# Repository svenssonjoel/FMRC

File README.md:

# FMRC (Work in progress)
Four Motor Robot Controller.

## General videos

[FMRC: UART communication between NRF52 and STM32!](https://youtu.be/KaF7SMBezBs)

## Firmware

### STM32F4 
* Work in progress

### NRF52
* TODO Start

* PROGRAMMING NRF52 stlink:  openocd -f interface/stlink.cfg -f target/nrf52.cfg

telnet localhost 4444
 > reset 
 > program zephyr.hex verify 

# V1_0

## Hardware

## PCBs arrived

## Ready to start testing

# V2_0

Work on version 2.0 is in progress. 

[FMRC V2 PART 14: First draft of completely routed PCB](https://youtu.be/DmLaImre3FM)

[FMRC V2 PART 13: More routing -- finishing off at the DRV8848 area](https://youtu.be/Vftj-5NWg6g )

[FMRC V2 PART 12: Starting to route in the DRV8848 area](https://youtu.be/RzzjTzkN7RY)

[FMRC V2 PART 11: More PCB routing](https://youtu.be/tmIGIp5ANTw)

[FMRC V2 PART 10: Started routing](https://youtu.be/_2mg14zOH1I)

[FMRC V2 PART 9: Tightening up the placement of components](https://youtu.be/uJEVWuKENiA)

[FMRC V2 PART 8: Roughly sorting components](https://youtu.be/DiCStZvnE-I)

[FMRC V2 PART 7: placing components focusing on the DC-DC area](https://youtu.be/_qIdTwvhaeo)

[FMRC V2 PART 6: Boot modes and Boot-loader that allows USB flashing](https://youtu.be/w9wKbaCBO-c)

[FMRC V2 PART 5: Adding an audio jack and doing some spice simulation in KiCAD](https://youtu.be/Df5hQqESk7Q)

[FMRC V2 PART 4: Servo outputs may be nice to have and finishing off in preparation for routing](https://youtu.be/peYSSjiu5AY)

[FMRC V2 PART 3: Out with the old, in with the new (and some confusion about pins with no net!)](https://youtu.be/iIYXo59sdyU)

[FMRC V2 PART 2B: Adding some caps and experimenting some more with kicad hierarchical labels](https://youtu.be/d1Me0BP48rM)

[FMRC V2 PART 2: Adding DRV8847 chips and trying out KICADs hiearchical labels](https://youtu.be/gP7LMV8jKK8)

[FMRC V2 PART 1: new 5V regulator that can do 3A](https://youtu.be/TqqdmnVX5Wo)

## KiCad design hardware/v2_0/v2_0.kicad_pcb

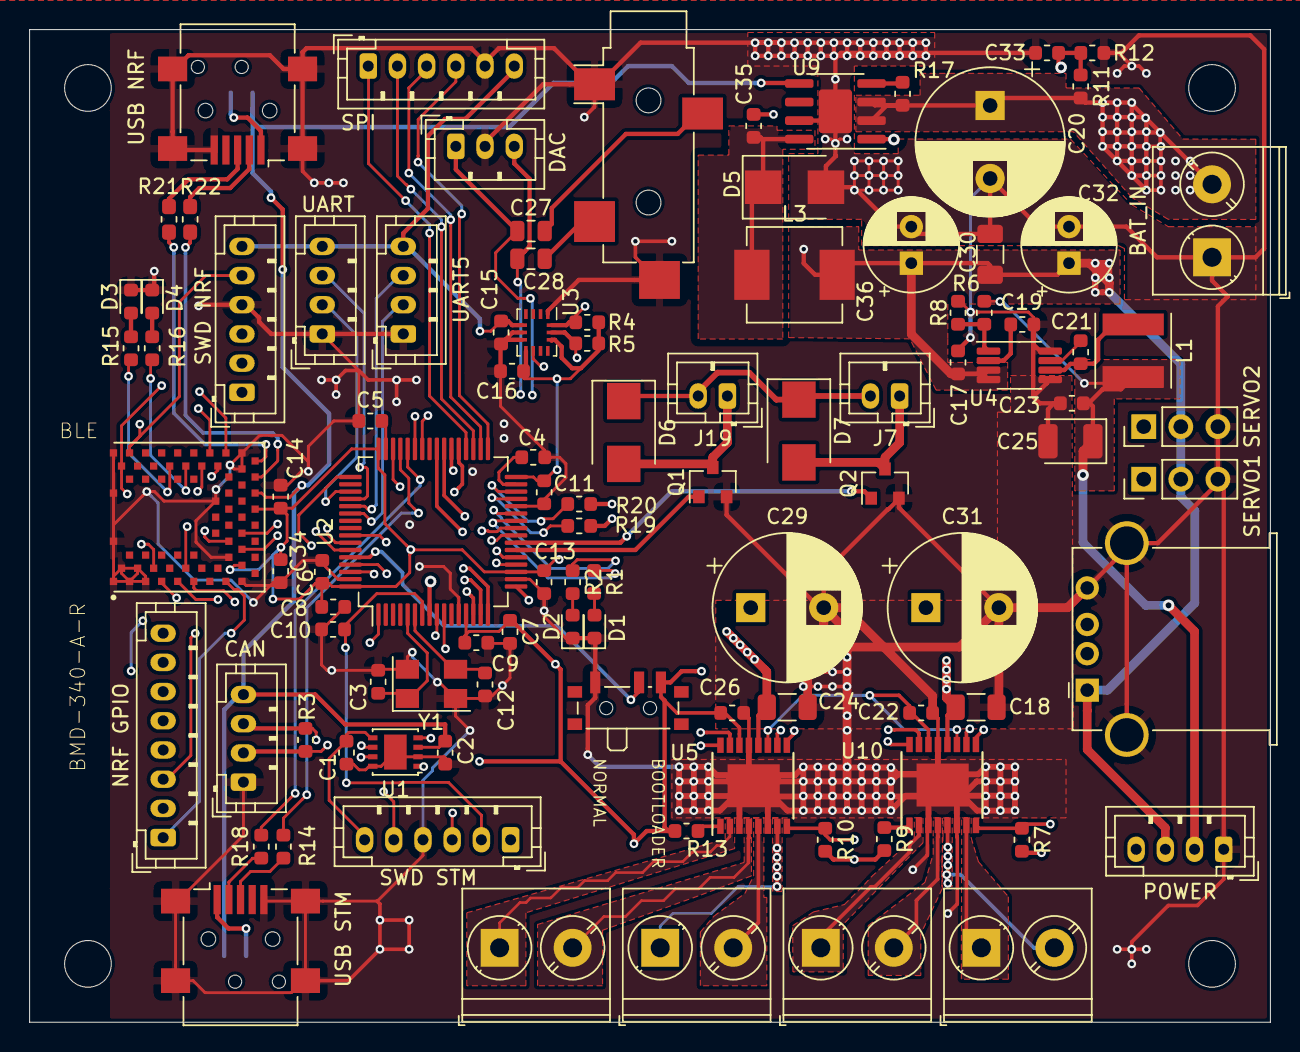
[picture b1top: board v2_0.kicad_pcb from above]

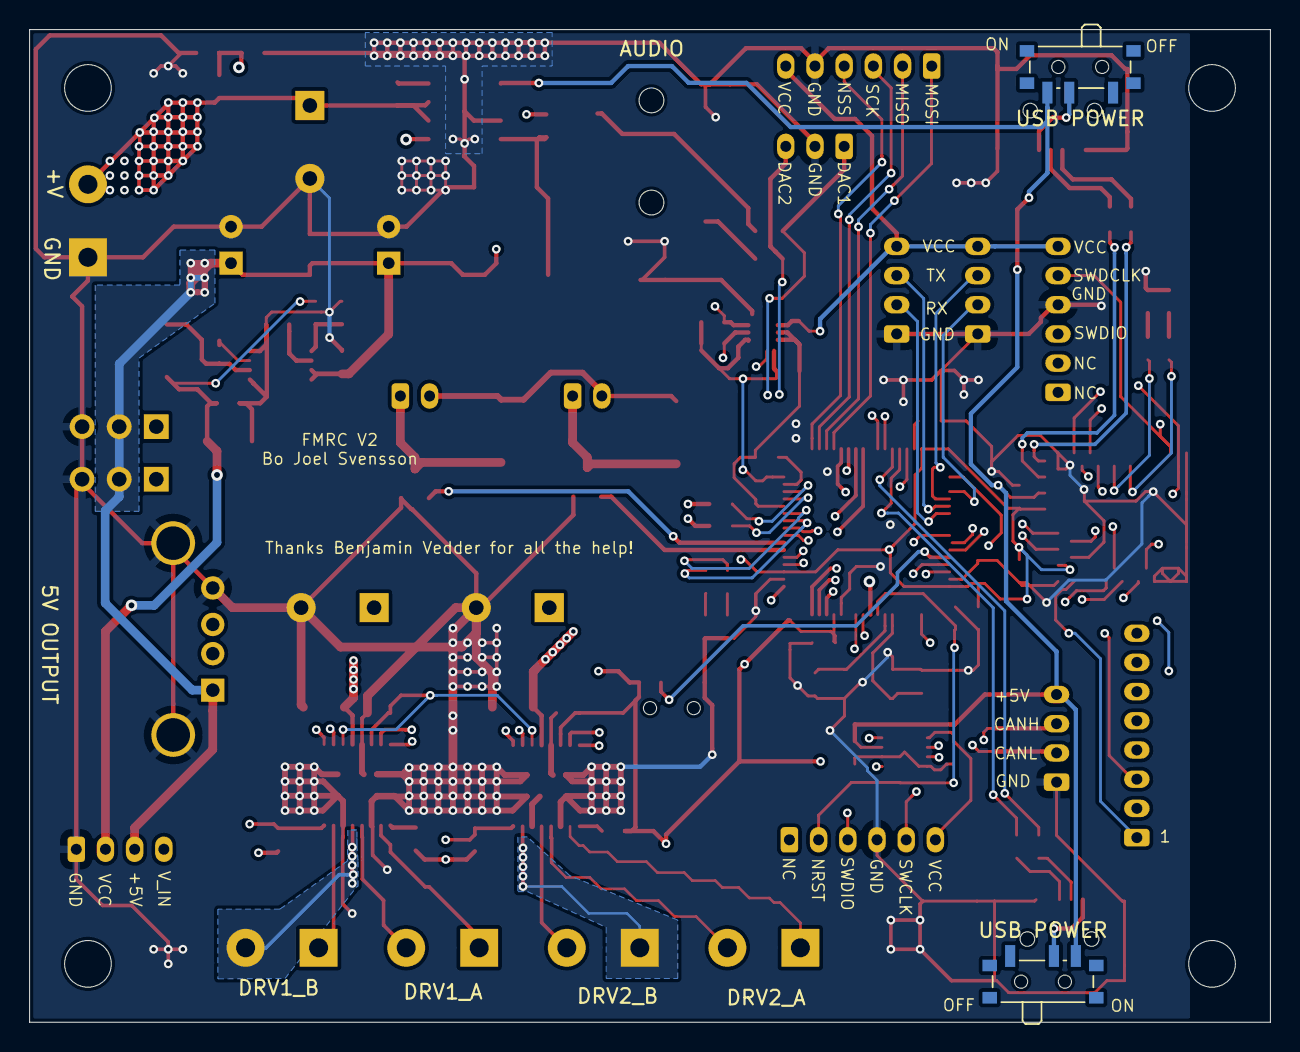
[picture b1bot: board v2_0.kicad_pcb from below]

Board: 4 copper layers, 85.0 x 68.0 mm, 107 parts (2 on the bottom side), 97 nets.

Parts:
5V OUTPUT: USB_A; USB_A_Stewart_SS-52100-001_Horizontal
AUDIO: AudioJack3_Ground; Jack_3.5mm_CUI_SJ-3524-SMT_Horizontal
BAT_IN: Power_terminal; TerminalBlock_Phoenix_PT-1,5-2-5.0-H_1x02_P5.00mm_Horizontal
BLE: BMD-340-A-R; RIGADO_BMD-340-A-R
C1, C2, C4, C5, C6, C7, C8, C9, C11, C13, C14, C15, C16, C17, C19, C22, C23, C26, C33, C34: 2.2u; C_0603_1608Metric
C3, C12: 15p; C_0603_1608Metric
C10, C21: 100n; C_0603_1608Metric
C18, C24, C30: 10uF; C_1206_3216Metric
C20, C29, C31: 100uF; CP_Radial_D10.0mm_P5.00mm
C25: 100u; CP_EIA-3528-12_Kemet-T
C27, C28: 10uF; C_0805_2012Metric
C32, C36: 47uF; CP_Radial_D6.3mm_P2.50mm
C35: 0.1uF; C_0603_1608Metric
CAN: CAN; JST_PH_B4B-PH-K_1x04_P2.00mm_Vertical
D1, D3: RED; LED_0603_1608Metric
D2, D4: GREEN; LED_0603_1608Metric
D5: SSB43L; D_SMB
D6, D7: D_Schottky; D_SMB
DAC: DAC; JST_PH_B3B-PH-K_1x03_P2.00mm_Vertical
DRV1_A, DRV2_A: DRV1_MTR1; TerminalBlock_Phoenix_PT-1,5-2-5.0-H_1x02_P5.00mm_Horizontal
DRV1_B, DRV2_B: DRV1_MTR2; TerminalBlock_Phoenix_PT-1,5-2-5.0-H_1x02_P5.00mm_Horizontal
J7: MTR2_CON; JST_PH_B2B-PH-K_1x02_P2.00mm_Vertical
J19: MTR1_CON; JST_PH_B2B-PH-K_1x02_P2.00mm_Vertical
L1: 22U; L_Taiyo-Yuden_MD-5050
L3: 4,7uH; L_Vishay_IHLP-2525
MK1, MK2, MK3, MK4: Mounting_Hole; MountingHole_3.2mm_M3
NRF GPIO: NRFGPIO; JST_PH_B8B-PH-K_1x08_P2.00mm_Vertical
POWER: PWR; JST_PH_B4B-PH-K_1x04_P2.00mm_Vertical
Q1, Q2: Q_NMOS_GSD; SOT-23
R1, R2, R4, R5, R15, R16: 1k; R_0603_1608Metric
R3, R19, R20: 220R; R_0603_1608Metric
R6: 33k; R_0603_1608Metric
R7, R8, R9, R10, R13: 10k; R_0603_1608Metric
R11: 56k; R_0603_1608Metric
R12: 12k; R_0603_1608Metric
R14, R18: 22R; R_0603_1608Metric
R17: 100k; R_0603_1608Metric
R21, R22: 22R; R_0603_1608Metric_Pad1.05x0.95mm_HandSolder
SERVO1: SERV1; PinHeader_1x03_P2.54mm_Vertical
SERVO2: SERV2; PinHeader_1x03_P2.54mm_Vertical
SPI: SPI; JST_PH_B6B-PH-K_1x06_P2.00mm_Vertical
SW3: BOOT0; SW_SPDT_PCM12
SWD NRF: NRFSWD; JST_PH_B6B-PH-K_1x06_P2.00mm_Vertical
SWD STM: SWD; JST_PH_B6B-PH-K_1x06_P2.00mm_Vertical
U1: TJA1051TK-3; DFN-8-1EP_3x3mm_P0.65mm_EP1.55x2.4mm
U2: STM32F40X_LQFP64; LQFP-64_10x10mm_P0.5mm
U3: BMI160; Bosch_LGA-14_3x2.5mm_P0.5mm
U4: MCP16311/2; MSOP-8_3x3mm_P0.65mm
U5, U10: DRV8848; TSSOP-16-1EP_4.4x5mm_P0.65mm
U9: ADP2303ARDZ-5.0; SOIC-8-1EP_3.9x4.9mm_P1.27mm_EP2.29x3mm
UART: USART3_UART4; JST_PH_B4B-PH-K_1x04_P2.00mm_Vertical
UART5: UART5; JST_PH_B4B-PH-K_1x04_P2.00mm_Vertical
USB NRF: USB_B_Mini; USB_Mini-B_Lumberg_2486_01_Horizontal
USB POWER: NRF_USB_POWER; SW_SPDT_PCM12
USB POWER#2: MCU_USB_POWER; SW_SPDT_PCM12
USB STM: USB_B_Mini; USB_Mini-B_Lumberg_2486_01_Horizontal
Y1: 8M; Crystal_SMD_5032-4Pin_5.0x3.2mm

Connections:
+5V: 5V OUTPUT.1, BLE.66, C2.1, C17.1, C30.1, C32.1, C36.1, CAN.4, L3.2, POWER.3, SERVO1.2, SERVO2.2, U1.3, U4.3, U4.4, U9.5, USB POWER.3, USB POWER#2.3
/DRV1_A1: U2.14, U10.16
/DRV1_A2: U2.15, U10.15
/DRV1_B1: U2.16, U10.9
/DRV1_B2: U2.17, U10.10
/DRV1_NFAULT: R7.1, U2.24, U10.8
/DRV2_A1: U2.37, U5.16
/DRV2_A2: U2.38, U5.15
/DRV2_B1: U2.39, U5.9
/DRV2_B2: U2.40, U5.10
/MTR1_PWM: Q1.1, U2.22
/MTR2_PWM: Q2.1, U2.23
/NFAULT_DRV2: R10.1, U2.25, U5.8
/base_sheet/BOOT0: SW3.2, U2.60
/base_sheet/SERV1: R19.1, U2.29
/base_sheet/SERV2: R20.1, U2.30
/base_sheet/SPI2_MISO: SPI.2, U2.35
/base_sheet/SPI2_MOSI: SPI.1, U2.36
/base_sheet/SPI2_NSS: SPI.4, U2.33
/base_sheet/SPI2_SCK: SPI.3, U2.34
/base_sheet/UART5_RX: U2.54, UART5.2
/base_sheet/UART5_TX: U2.53, UART5.3
CANH: CAN.3, R3.2, U1.7
CANL: CAN.2, R3.1, U1.6
CAN_RX: U1.4, U2.61
CAN_TX: U1.1, U2.62
GND: 5V OUTPUT.4, 5V OUTPUT.5, AUDIO.G, AUDIO.S, BAT_IN.1, BLE.1, BLE.2, BLE.3, BLE.4, BLE.5, BLE.16, BLE.18, BLE.29, BLE.30, BLE.45, BLE.46, BLE.47, BLE.55, C1.2, C2.2, C3.1, C4.1, C5.1, C6.2, C7.2, C8.2, C9.2, C10.2, C11.2, C12.1, C13.2, C14.2, C15.2, C16.2, C17.2, C18.1, C19.2, C20.2, C22.2, C23.2, C24.1, C25.2, C26.2, C29.2, C30.2, C31.2, C32.2, C33.1, C34.2, C36.2, CAN.1, D1.1, D2.1, D3.1, D4.1, D5.2, DAC.2, POWER.1, Q1.2, Q2.2, R8.1, R12.2, SERVO1.3, SERVO2.3, SPI.5, SW3.1, SWD NRF.4, SWD STM.4, U1.2, U1.8, U1.9, U2.12, U2.18, U2.28, U2.63, U3.1, U3.6, U3.7, U4.5, U4.8, U5.3, U5.6, U5.13, U5.17, U9.7, U9.9, U10.3, U10.6, U10.13, U10.17, UART.1, UART5.1, USB NRF.5, USB NRF.6, USB STM.5, USB STM.6, Y1.2, Y1.4
IMU_INT2: BLE.11, U2.57, U3.9
NRFGPIO1: BLE.15, NRF GPIO.1
NRFGPIO2: BLE.19, NRF GPIO.2
NRFGPIO3: BLE.20, NRF GPIO.3
NRFGPIO4: BLE.21, NRF GPIO.4
NRFGPIO5: BLE.31, NRF GPIO.5
NRFGPIO6: BLE.32, NRF GPIO.6
NRFGPIO7: BLE.33, NRF GPIO.7
NRFGPIO8: BLE.34, NRF GPIO.8
NRFRX: BLE.7, U2.42
NRFSWDCLK: BLE.43, SWD NRF.5, U2.10
NRFSWDIO: BLE.44, SWD NRF.3, U2.9
NRFTX: BLE.6, U2.43
NRFUSBD+: BLE.68, R21.2
NRFUSBD-: BLE.67, R22.2
NRST: C10.1, SWD STM.2, U2.7
unnamed: C3.2, U2.5, Y1.1
unnamed: C4.2, U2.31
unnamed: C5.2, U2.47
unnamed: C12.2, U2.6, Y1.3
unnamed: C19.1, U4.2
unnamed: C21.1, U4.7
unnamed: C21.2, L1.1, U4.6
unnamed: C27.1, DAC.1, U2.20
unnamed: AUDIO.R, C27.2
unnamed: C28.1, DAC.3, U2.21
unnamed: AUDIO.T, C28.2
unnamed: C35.1, U9.1
unnamed: C35.2, D5.1, L3.1, U9.8
unnamed: D1.2, R1.2
unnamed: D2.2, R2.2
unnamed: D3.2, R15.2
unnamed: D4.2, R16.2
unnamed: D6.2, J19.1, Q1.3
unnamed: D7.2, J7.1, Q2.3
unnamed: USB POWER#2.2, USB STM.1
unnamed: R18.1, USB STM.2
unnamed: R14.1, USB STM.3
unnamed: DRV1_A.1, U10.2
unnamed: DRV1_A.2, U10.4
unnamed: DRV1_B.1, U10.7
unnamed: DRV1_B.2, U10.5
unnamed: DRV2_A.1, U5.2
unnamed: DRV2_A.2, U5.4
unnamed: R19.2, SERVO1.1
unnamed: R20.2, SERVO2.1
unnamed: USB NRF.1, USB POWER.2
unnamed: R22.1, USB NRF.2
unnamed: R21.1, USB NRF.3
unnamed: DRV2_B.1, U5.7
unnamed: DRV2_B.2, U5.5
unnamed: R1.1, U2.26
unnamed: R2.1, U2.27
unnamed: R6.1, R8.2, U4.1
unnamed: R9.1, U10.1
unnamed: R13.1, U5.1
unnamed: BLE.38, R15.1
unnamed: BLE.36, R16.1
unnamed: R17.2, U9.4
SCL: BLE.10, R5.1, U2.58, U3.13
SDA: BLE.9, R4.1, U2.59, U3.14
SWCLK: SWD STM.5, U2.49
SWDIO: SWD STM.3, U2.46
UART_RXD: U2.51, UART.2
UART_TXD: U2.52, UART.3
USB_DM: R18.2, U2.44
USB_DP: R14.2, U2.45
VCC: BLE.17, BLE.65, C1.1, C6.1, C7.1, C8.1, C9.1, C11.1, C13.1, C14.1, C15.1, C16.1, C22.1, C23.1, C25.1, C26.1, C34.1, L1.2, POWER.2, R4.2, R5.2, R6.2, R7.2, R9.2, R10.2, R13.2, SPI.6, SW3.3, SWD NRF.6, SWD STM.6, U1.5, U2.1, U2.13, U2.19, U2.32, U2.48, U2.64, U3.5, U3.8, U3.12, U5.11, U5.14, U10.11, U10.14, UART.4, UART5.4
V_IN: BAT_IN.2, C18.2, C20.1, C24.2, C29.1, C31.1, D6.1, D7.1, J7.2, J19.2, POWER.4, R11.2, R17.1, U5.12, U9.2, U9.3, U10.12
V_METER: C33.2, R11.1, R12.1, U2.8

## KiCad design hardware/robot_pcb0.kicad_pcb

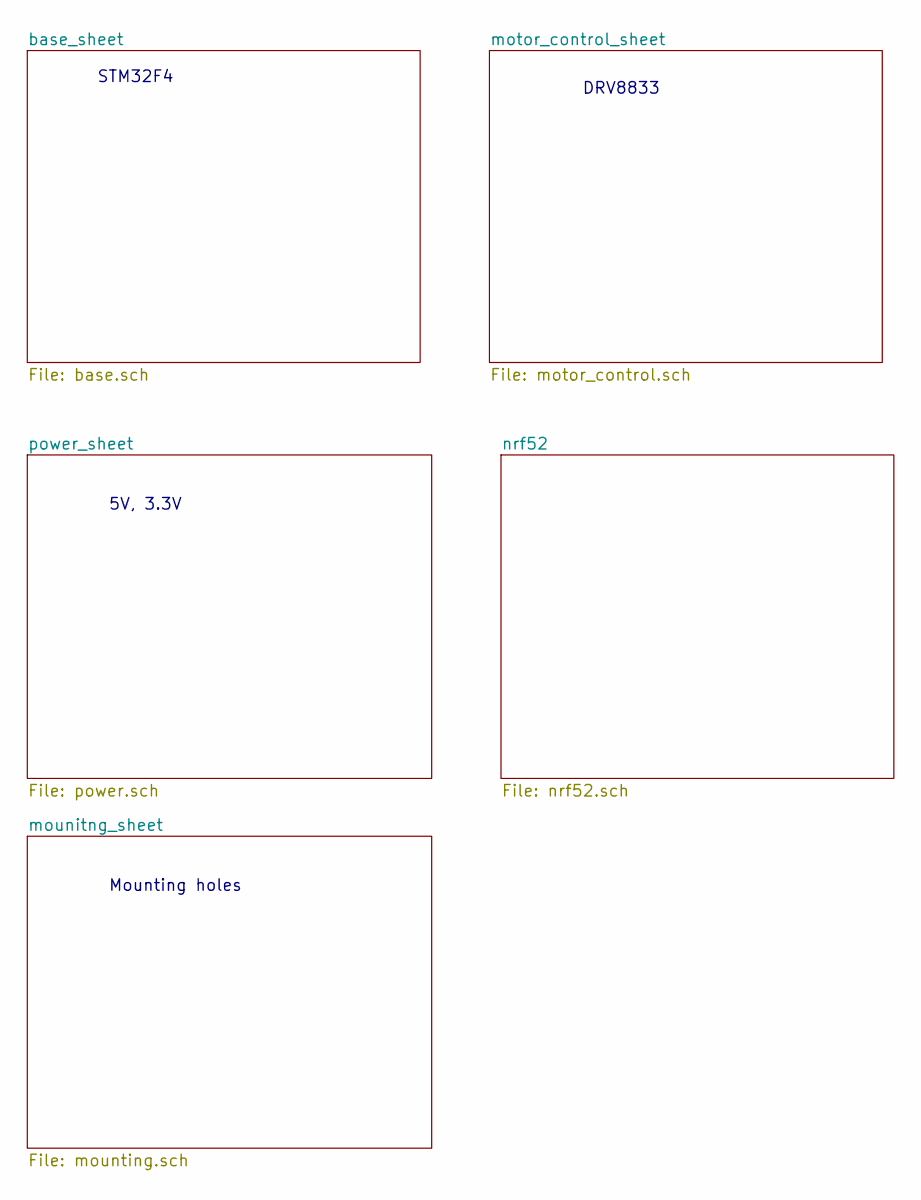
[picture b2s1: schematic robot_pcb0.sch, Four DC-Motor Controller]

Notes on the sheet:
STM32F4
5V, 3.3V
Mounting holes
DRV8833

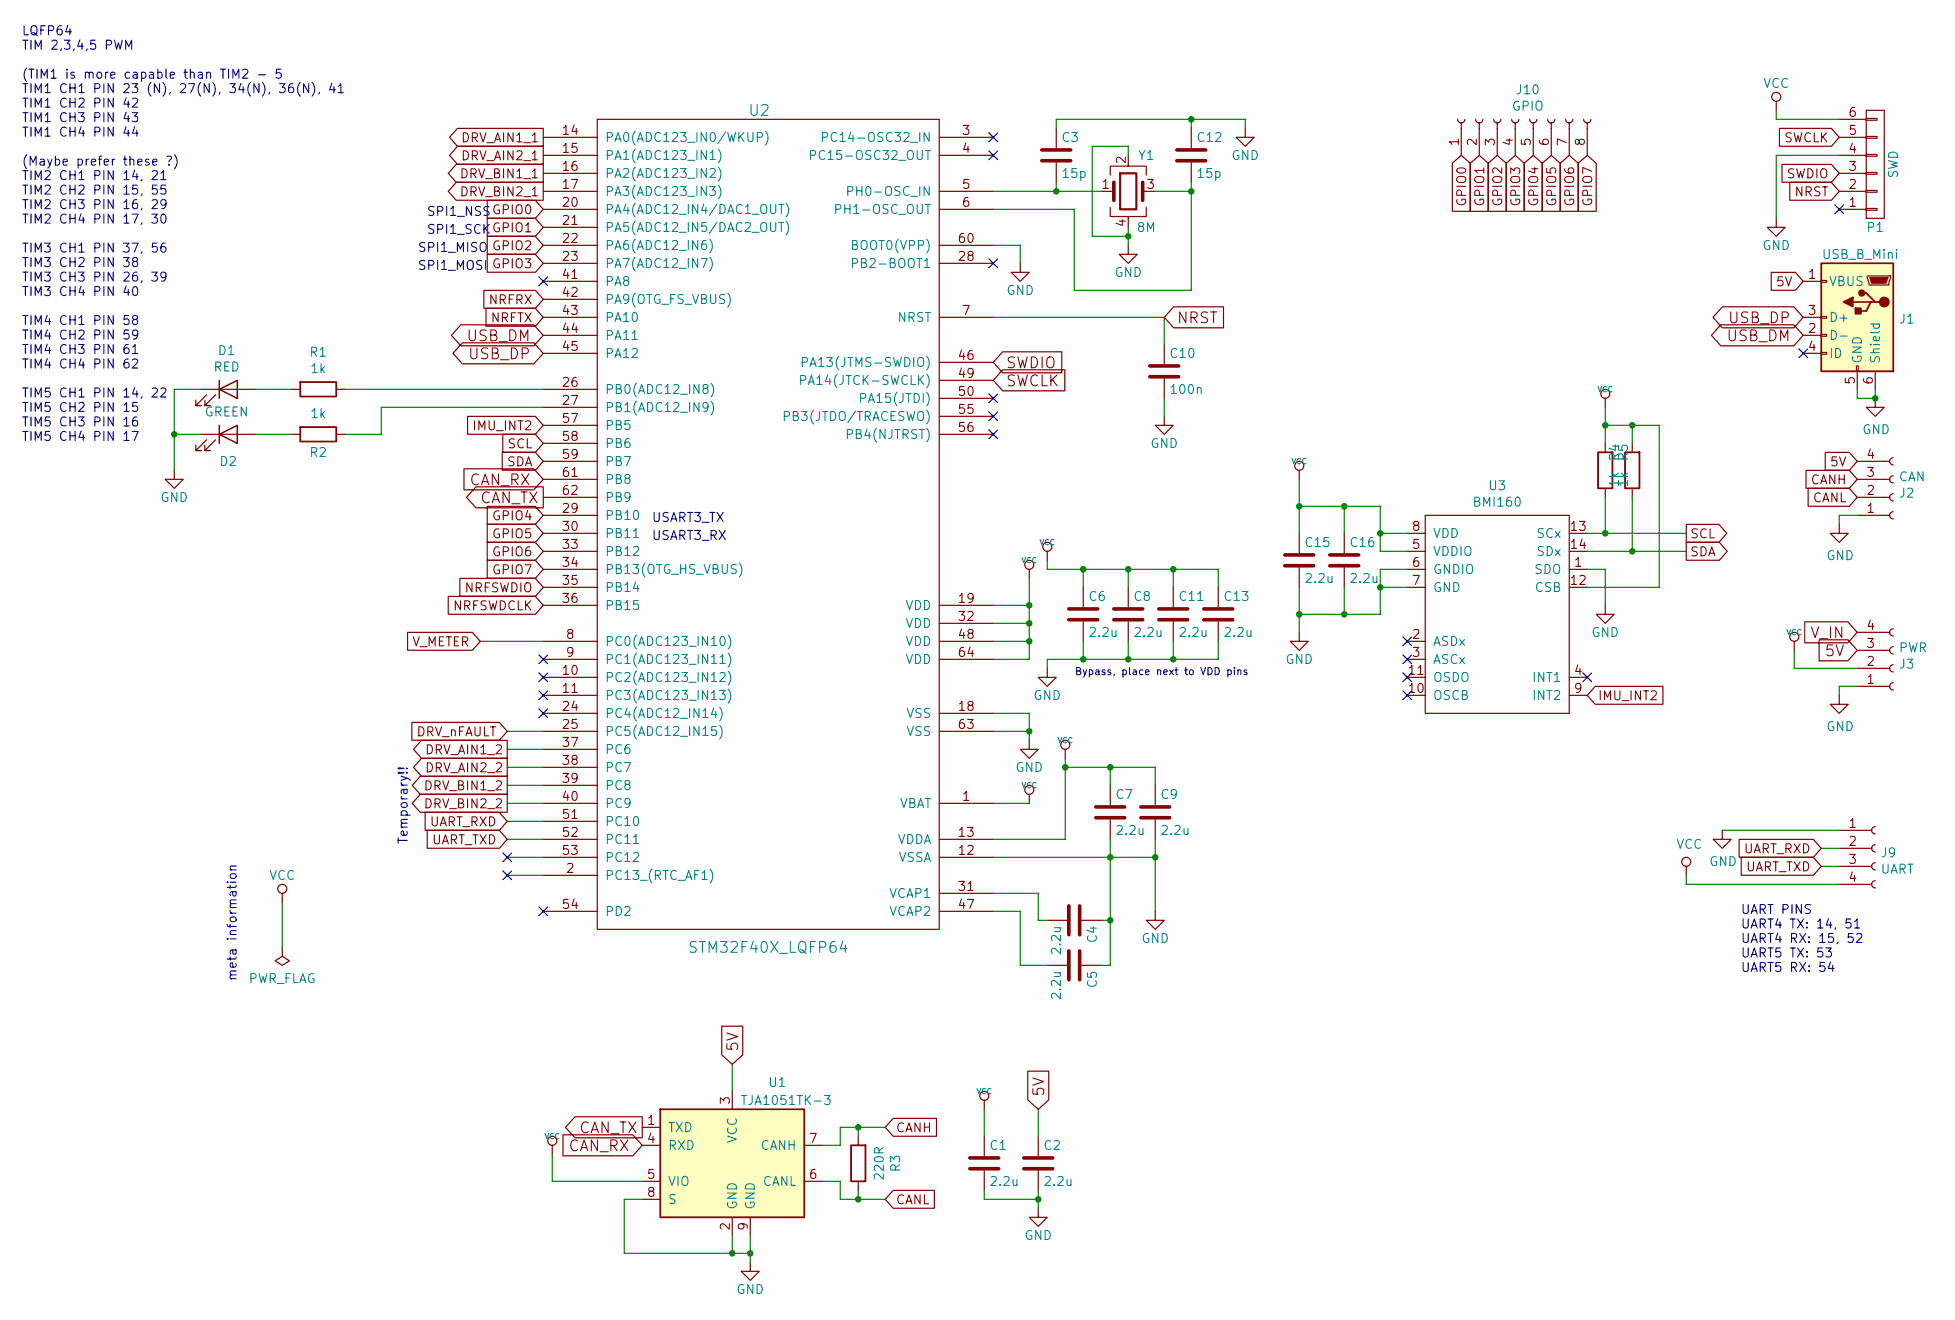
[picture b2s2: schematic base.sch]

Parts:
C1, C2, C4, C5, C6, C7, C8, C9, C11, C13, C15, C16: 2.2u; C_0603_1608Metric
C3, C12: 15p; C_0603_1608Metric
C10: 100n; C_0603_1608Metric
D1: RED; LED_0603_1608Metric
D2: GREEN; LED_0603_1608Metric
J1: USB_B_Mini; USB_Mini-B_Lumberg_2486_01_Horizontal
J2: CAN; JST_PH_B4B-PH-K_1x04_P2.00mm_Vertical
J3: PWR; JST_PH_B4B-PH-K_1x04_P2.00mm_Vertical
J9: UART; JST_PH_B4B-PH-K_1x04_P2.00mm_Vertical
J10: GPIO; JST_PH_B8B-PH-K_1x08_P2.00mm_Vertical
P1: SWD; JST_PH_B6B-PH-K_1x06_P2.00mm_Vertical
R1, R2, R4, R5: 1k; R_0603_1608Metric
R3: 220R; R_0603_1608Metric
U1: TJA1051TK-3; DFN-8-1EP_3x3mm_P0.65mm_EP1.55x2.4mm
U2: STM32F40X_LQFP64; LQFP-64_10x10mm_P0.5mm
U3: BMI160; Bosch_LGA-14_3x2.5mm_P0.5mm
Y1: 8M; Crystal_SMD_5032-4Pin_5.0x3.2mm

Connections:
5V: C2.1, J1.1 (VBUS), J2.4, J3.3, U1.3 (VCC); also elsewhere on the board
CANH: J2.3, R3.2, U1.7 (CANH)
CANL: J2.2, R3.1, U1.6 (CANL)
CAN_RX: U1.4 (RXD), U2.61 (PB8)
CAN_TX: U1.1 (TXD), U2.62 (PB9)
DRV_AIN1_1: U2.14 (PA0(ADC123_IN0/WKUP)); also elsewhere on the board
DRV_AIN1_2: U2.37 (PC6); also elsewhere on the board
DRV_AIN2_1: U2.15 (PA1(ADC123_IN1)); also elsewhere on the board
DRV_AIN2_2: U2.38 (PC7); also elsewhere on the board
DRV_BIN1_1: U2.16 (PA2(ADC123_IN2)); also elsewhere on the board
DRV_BIN1_2: U2.39 (PC8); also elsewhere on the board
DRV_BIN2_1: U2.17 (PA3(ADC123_IN3)); also elsewhere on the board
DRV_BIN2_2: U2.40 (PC9); also elsewhere on the board
DRV_nFAULT: U2.25 (PC5(ADC12_IN15)); also elsewhere on the board
GND: C1.2, C2.2, C3.1, C4.1, C5.1, C6.2, C7.2, C8.2, C9.2, C10.2, C11.2, C12.1, C13.2, C15.2, C16.2, D1.1 (K), D2.1 (K), J1.5 (GND), J1.6 (Shield), J2.1, J3.1, J9.1, P1.4, U1.2 (GND), U1.8 (S), U1.9 (GND), U2.12 (VSSA), U2.18 (VSS), U2.60 (BOOT0(VPP)), U2.63 (VSS), U3.1 (SDO), U3.6 (GNDIO), U3.7 (GND), Y1.2, Y1.4; also elsewhere on the board
GPIO0: J10.1, U2.20 (PA4(ADC12_IN4/DAC1_OUT))
GPIO1: J10.2, U2.21 (PA5(ADC12_IN5/DAC2_OUT))
GPIO2: J10.3, U2.22 (PA6(ADC12_IN6))
GPIO3: J10.4, U2.23 (PA7(ADC12_IN7))
GPIO4: J10.5, U2.29 (PB10)
GPIO5: J10.6, U2.30 (PB11)
GPIO6: J10.7, U2.33 (PB12)
GPIO7: J10.8, U2.34 (PB13(OTG_HS_VBUS))
IMU_INT2: U2.57 (PB5), U3.9 (INT2); also elsewhere on the board
NRFRX: U2.42 (PA9(OTG_FS_VBUS)); also elsewhere on the board
NRFSWDCLK: U2.36 (PB15); also elsewhere on the board
NRFSWDIO: U2.35 (PB14); also elsewhere on the board
NRFTX: U2.43 (PA10); also elsewhere on the board
NRST: C10.1, P1.2, U2.7 (NRST)
unnamed: C3.2, U2.5 (PH0-OSC_IN), Y1.1
unnamed: C4.2, U2.31 (VCAP1)
unnamed: C5.2, U2.47 (VCAP2)
unnamed: C12.2, U2.6 (PH1-OSC_OUT), Y1.3
unnamed: D1.2 (A), R1.2
unnamed: D2.2 (A), R2.2
unnamed: R1.1, U2.26 (PB0(ADC12_IN8))
unnamed: R2.1, U2.27 (PB1(ADC12_IN9))
SCL: R5.1, U2.58 (PB6), U3.13 (SCx); also elsewhere on the board
SDA: R4.1, U2.59 (PB7), U3.14 (SDx); also elsewhere on the board
SWCLK: P1.5, U2.49 (PA14(JTCK-SWCLK))
SWDIO: P1.3, U2.46 (PA13(JTMS-SWDIO))
UART_RXD: J9.2, U2.51 (PC10)
UART_TXD: J9.3, U2.52 (PC11)
USB_DM: J1.2 (D-), U2.44 (PA11)
USB_DP: J1.3 (D+), U2.45 (PA12)
VCC: C1.1, C6.1, C7.1, C8.1, C9.1, C11.1, C13.1, C15.1, C16.1, J3.2, J9.4, P1.6, R4.2, R5.2, U1.5 (VIO), U2.1 (VBAT), U2.13 (VDDA), U2.19 (VDD), U2.32 (VDD), U2.48 (VDD), U2.64 (VDD), U3.5 (VDDIO), U3.8 (VDD), U3.12 (CSB); also elsewhere on the board
V_IN: J3.4; also elsewhere on the board
V_METER: U2.8 (PC0(ADC123_IN10)); also elsewhere on the board

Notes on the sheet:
Bypass, place next to VDD pins
meta information
Temporary!!
UART PINS UART4 TX: 14, 51 UART4 RX: 15, 52 UART5 TX: 53 UART5 RX: 54
USART3_TX
USART3_RX
SPI1_NSS
SPI1_SCK
SPI1_MISO
SPI1_MOSI
LQFP64 TIM 2,3,4,5 PWM (TIM1 is more capable than TIM2 - 5 TIM1 CH1 PIN 23 (N), 27(N), 34(N), 36(N), 41 TIM1 CH2 PIN 42 TIM1 CH3 PIN 43 TIM1 CH4 PIN 44 (Maybe prefer these ?) TIM2 CH1 PIN 14, 21 TIM2 CH2 PIN 15, 55 TIM2 CH3 PIN 16, 29 TIM2 CH4 PIN 17, 30 TIM3 CH1 PIN 37, 56 TIM3 CH2 PIN 38 TIM3 CH3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

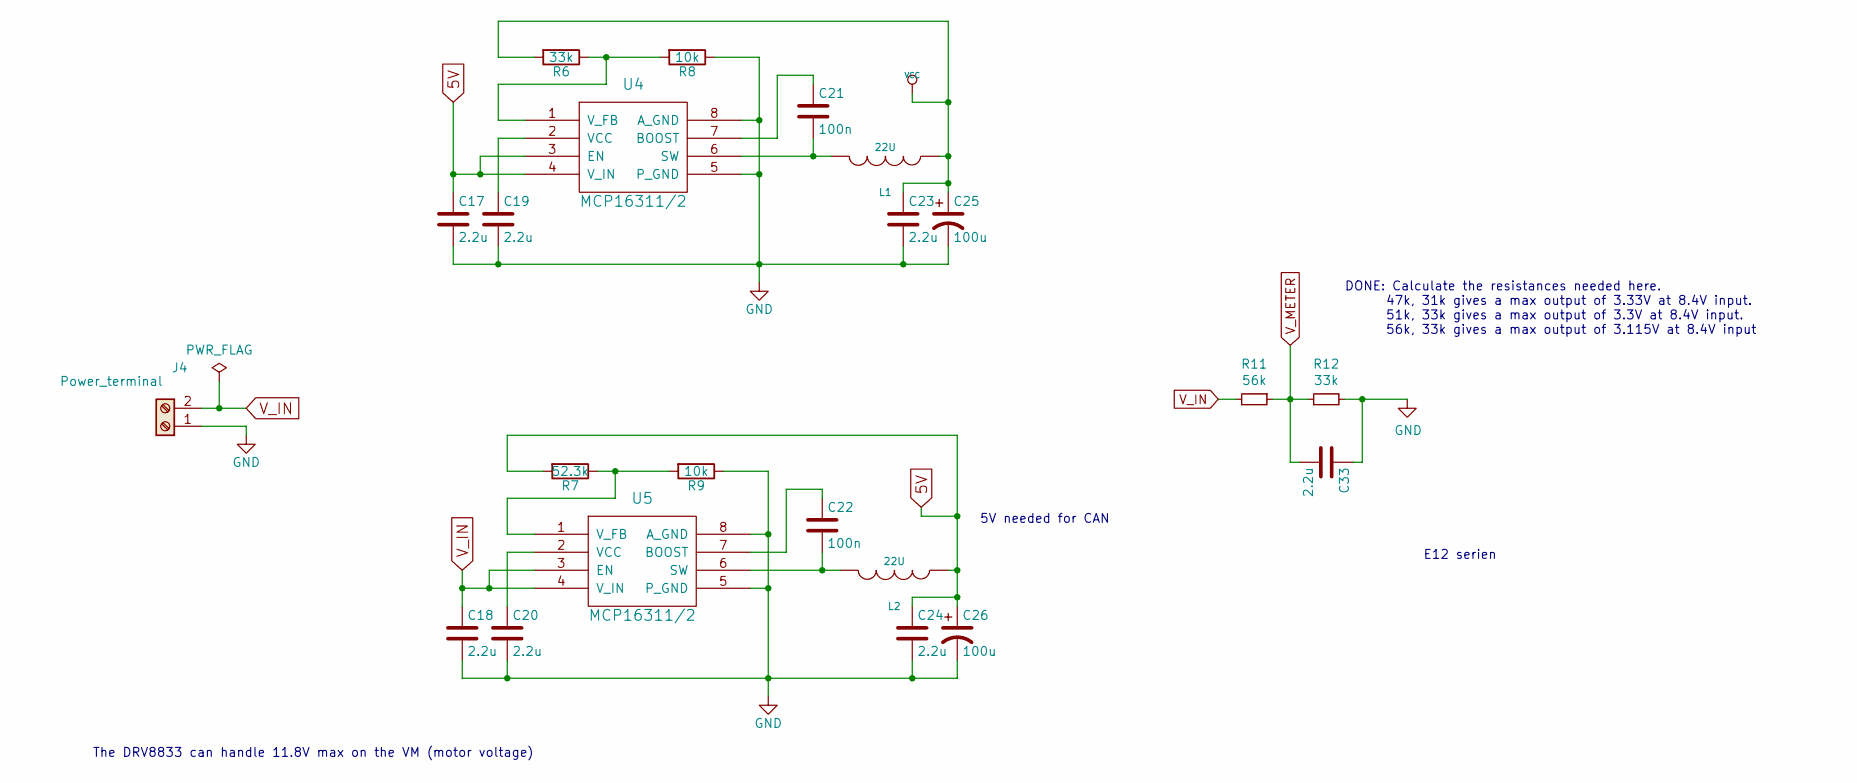
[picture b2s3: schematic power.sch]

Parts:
C17, C18, C19, C20, C23, C24, C33: 2.2u; C_0603_1608Metric
C21, C22: 100n; C_0603_1608Metric
C25, C26: 100u; CP_EIA-3528-12_Kemet-T
J4: Power_terminal; TerminalBlock_Phoenix_PT-1,5-2-5.0-H_1x02_P5.00mm_Horizontal
L1, L2: 22U; L_Taiyo-Yuden_MD-5050
R6, R12: 33k; R_0603_1608Metric
R7: 52.3k; R_0603_1608Metric
R8, R9: 10k; R_0603_1608Metric
R11: 56k; R_0603_1608Metric
U4, U5: MCP16311/2; MSOP-8_3x3mm_P0.65mm

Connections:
5V: C17.1, C24.1, C26.1, L2.1, R7.2, U4.3 (EN), U4.4 (V_IN); also elsewhere on the board
GND: C17.2, C18.2, C19.2, C20.2, C23.2, C24.2, C25.2, C26.2, C33.1, J4.1, R8.1, R9.1, R12.2, U4.5 (P_GND), U4.8 (A_GND), U5.5 (P_GND), U5.8 (A_GND); also elsewhere on the board
unnamed: C19.1, U4.2 (VCC)
unnamed: C20.1, U5.2 (VCC)
unnamed: C21.1, U4.7 (BOOST)
unnamed: C21.2, L1.2, U4.6 (SW)
unnamed: C22.1, U5.7 (BOOST)
unnamed: C22.2, L2.2, U5.6 (SW)
unnamed: R6.1, R8.2, U4.1 (V_FB)
unnamed: R7.1, R9.2, U5.1 (V_FB)
VCC: C23.1, C25.1, L1.1, R6.2; also elsewhere on the board
V_IN: C18.1, J4.2, R11.2, U5.3 (EN), U5.4 (V_IN); also elsewhere on the board
V_METER: C33.2, R11.1, R12.1; also elsewhere on the board

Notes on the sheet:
DONE: Calculate the resistances needed here. 47k, 31k gives a max output of 3.33V at 8.4V input. 51k, 33k gives a max output of 3.3V at 8.4V input. 56k, 33k gives a max output of 3.115V at 8.4V input
5V needed for CAN
E12 serien
The DRV8833 can handle 11.8V max on the VM (motor voltage)

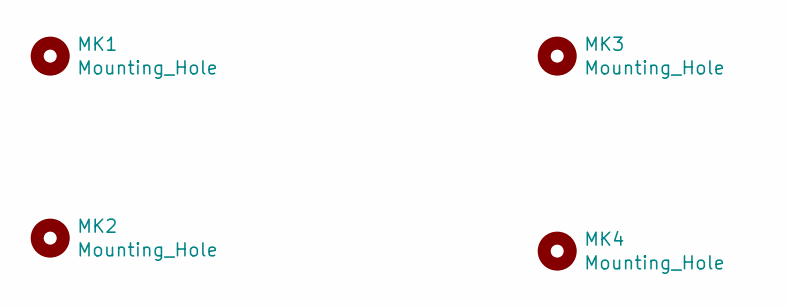
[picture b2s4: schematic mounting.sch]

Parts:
MK1, MK2, MK3, MK4: Mounting_Hole; MountingHole_3.2mm_M3

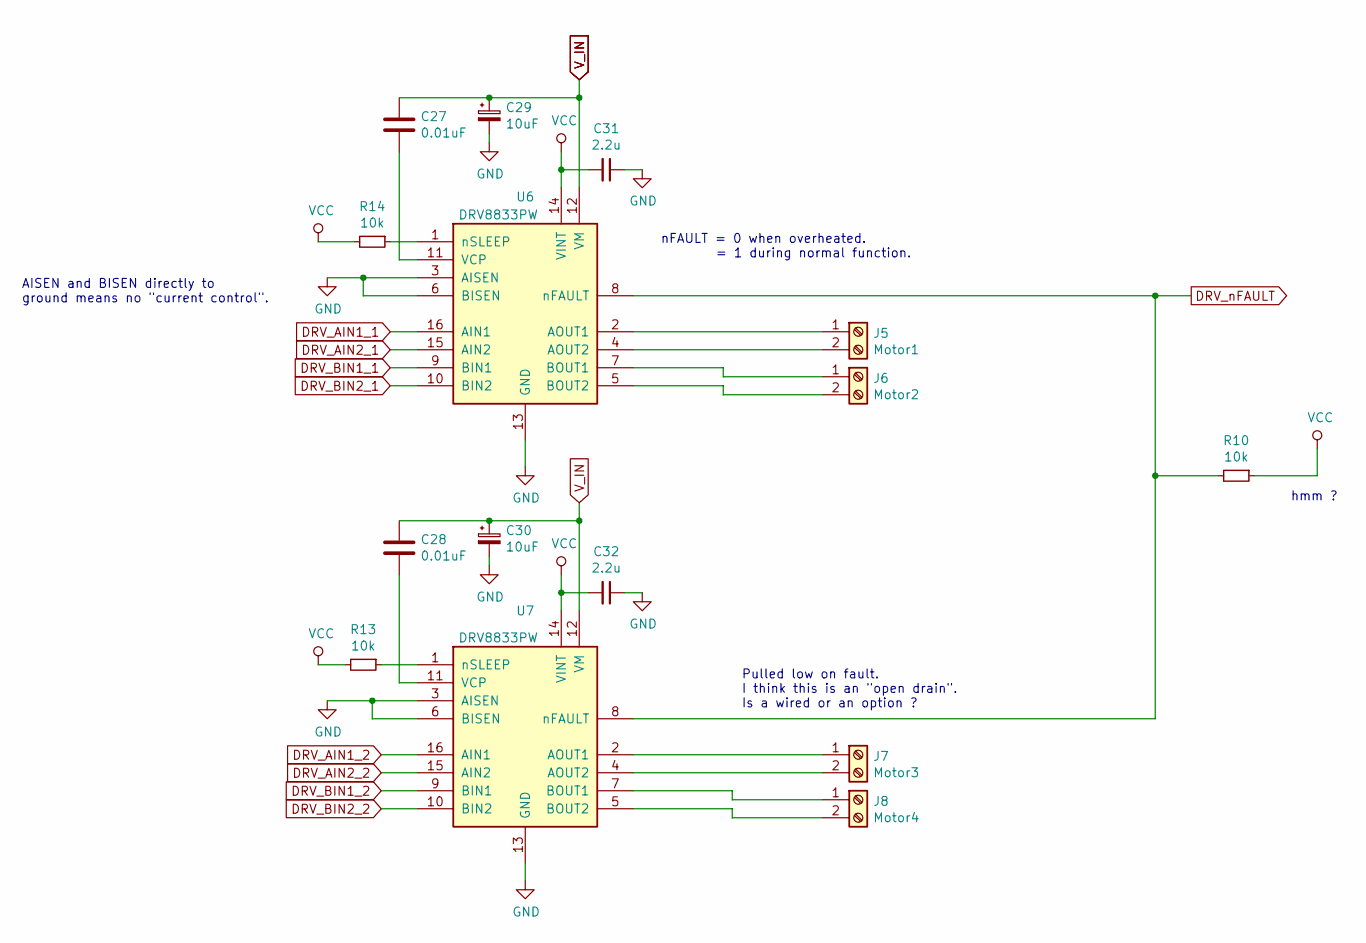
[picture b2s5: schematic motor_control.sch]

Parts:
C27, C28: 0.01uF; C_0603_1608Metric
C29, C30: 10uF; C_0603_1608Metric
C31, C32: 2.2u; C_0603_1608Metric
J5: Motor1; TerminalBlock_Phoenix_PT-1,5-2-5.0-H_1x02_P5.00mm_Horizontal
J6: Motor2; TerminalBlock_Phoenix_PT-1,5-2-5.0-H_1x02_P5.00mm_Horizontal
J7: Motor3; TerminalBlock_Phoenix_PT-1,5-2-5.0-H_1x02_P5.00mm_Horizontal
J8: Motor4; TerminalBlock_Phoenix_PT-1,5-2-5.0-H_1x02_P5.00mm_Horizontal
R10, R13, R14: 10k; R_0603_1608Metric
U6, U7: DRV8833PW; TSSOP-16_4.4x5mm_P0.65mm

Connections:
DRV_AIN1_1: U6.16 (AIN1); also elsewhere on the board
DRV_AIN1_2: U7.16 (AIN1); also elsewhere on the board
DRV_AIN2_1: U6.15 (AIN2); also elsewhere on the board
DRV_AIN2_2: U7.15 (AIN2); also elsewhere on the board
DRV_BIN1_1: U6.9 (BIN1); also elsewhere on the board
DRV_BIN1_2: U7.9 (BIN1); also elsewhere on the board
DRV_BIN2_1: U6.10 (BIN2); also elsewhere on the board
DRV_BIN2_2: U7.10 (BIN2); also elsewhere on the board
DRV_nFAULT: R10.2, U6.8 (nFAULT), U7.8 (nFAULT); also elsewhere on the board
GND: C29.2, C30.2, C31.1, C32.1, U6.3 (AISEN), U6.6 (BISEN), U6.13 (GND), U7.3 (AISEN), U7.6 (BISEN), U7.13 (GND); also elsewhere on the board
unnamed: C27.2, U6.11 (VCP)
unnamed: C28.2, U7.11 (VCP)
unnamed: J5.1, U6.2 (AOUT1)
unnamed: J5.2, U6.4 (AOUT2)
unnamed: J6.1, U6.7 (BOUT1)
unnamed: J6.2, U6.5 (BOUT2)
unnamed: J7.1, U7.2 (AOUT1)
unnamed: J7.2, U7.4 (AOUT2)
unnamed: J8.1, U7.7 (BOUT1)
unnamed: J8.2, U7.5 (BOUT2)
unnamed: R13.1, U7.1 (nSLEEP)
unnamed: R14.1, U6.1 (nSLEEP)
VCC: C31.2, C32.2, R10.1, R13.2, R14.2, U6.14 (VINT), U7.14 (VINT); also elsewhere on the board
V_IN: C27.1, C28.1, C29.1, C30.1, U6.12 (VM), U7.12 (VM); also elsewhere on the board

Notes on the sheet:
AISEN and BISEN directly to ground means no "current control".
nFAULT = 0 when overheated. = 1 during normal function.
Pulled low on fault. I think this is an "open drain". Is a wired or an option ?
hmm ?

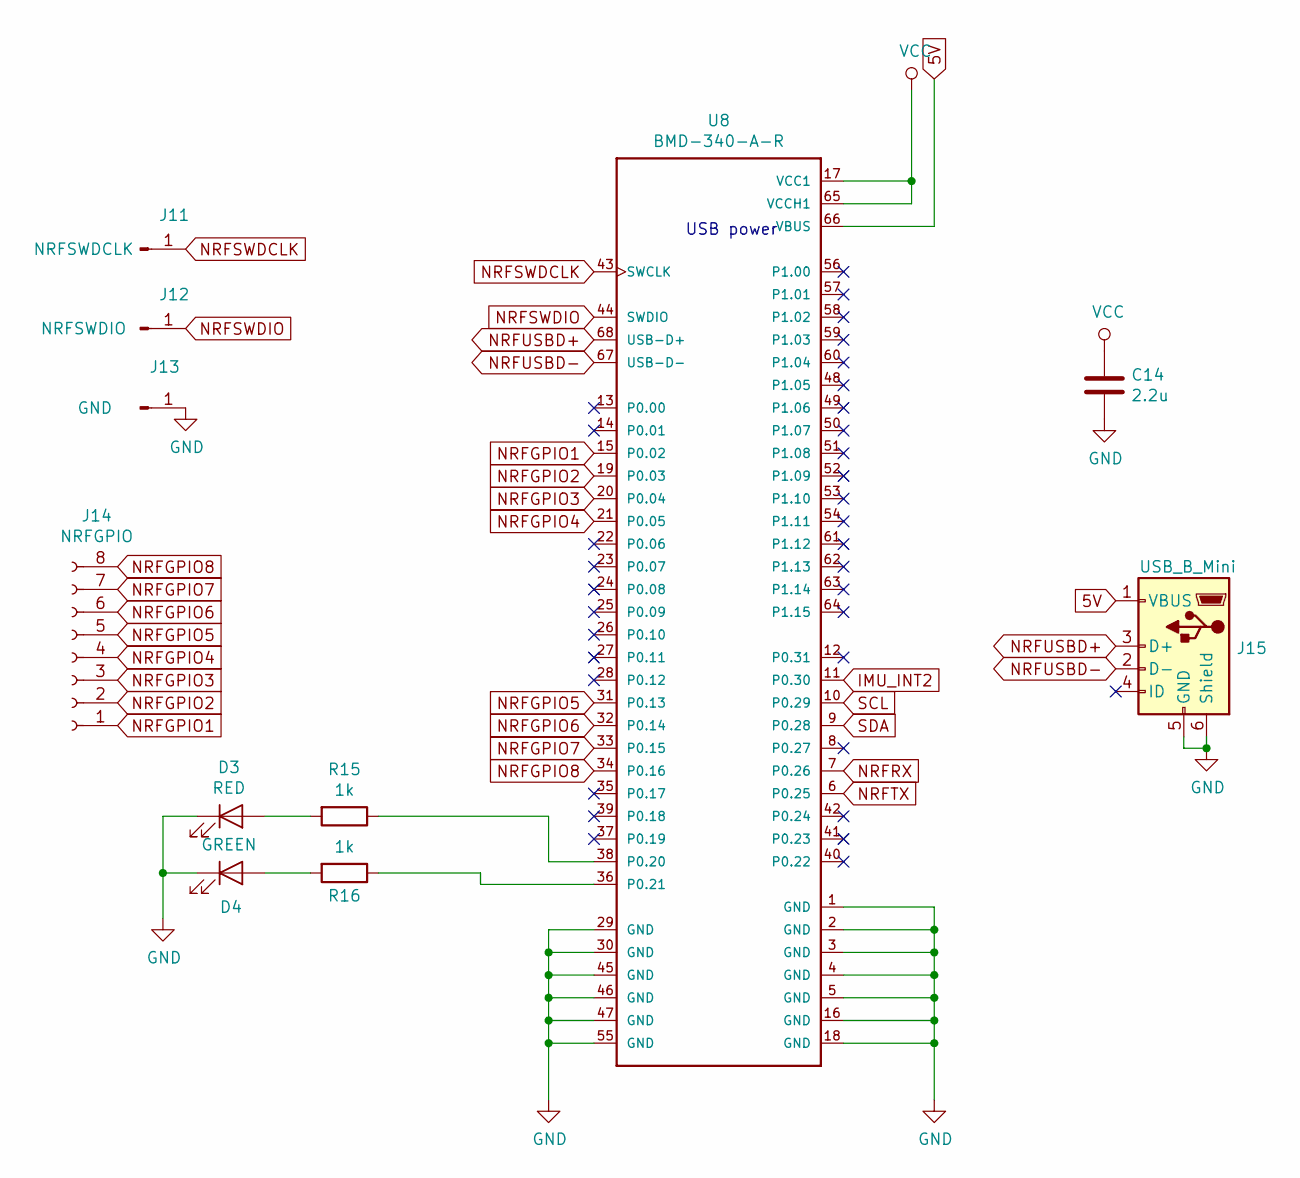
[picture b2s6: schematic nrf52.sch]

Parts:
C14: 2.2u; C_0603_1608Metric
D3: RED; LED_0603_1608Metric
D4: GREEN; LED_0603_1608Metric
J11: NRFSWDCLK; TestPoint_Pad_1.5x1.5mm
J12: NRFSWDIO; TestPoint_Pad_1.5x1.5mm
J13: GND; TestPoint_Pad_1.5x1.5mm
J14: NRFGPIO; JST_PH_B8B-PH-K_1x08_P2.00mm_Vertical
J15: USB_B_Mini; USB_Mini-B_Lumberg_2486_01_Horizontal
R15, R16: 1k; R_0603_1608Metric
U8: BMD-340-A-R; RIGADO_BMD-340-A-R

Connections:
5V: J15.1 (VBUS), U8.66 (VBUS); also elsewhere on the board
GND: C14.2, D3.1 (K), D4.1 (K), J13.1, J15.5 (GND), J15.6 (Shield), U8.1 (GND), U8.2 (GND), U8.3 (GND), U8.4 (GND), U8.5 (GND), U8.16 (GND), U8.18 (GND), U8.29 (GND), U8.30 (GND), U8.45 (GND), U8.46 (GND), U8.47 (GND), U8.55 (GND); also elsewhere on the board
IMU_INT2: U8.11 (P0.30); also elsewhere on the board
NRFGPIO1: J14.1, U8.15 (P0.02)
NRFGPIO2: J14.2, U8.19 (P0.03)
NRFGPIO3: J14.3, U8.20 (P0.04)
NRFGPIO4: J14.4, U8.21 (P0.05)
NRFGPIO5: J14.5, U8.31 (P0.13)
NRFGPIO6: J14.6, U8.32 (P0.14)
NRFGPIO7: J14.7, U8.33 (P0.15)
NRFGPIO8: J14.8, U8.34 (P0.16)
NRFRX: U8.7 (P0.26); also elsewhere on the board
NRFSWDCLK: J11.1, U8.43 (SWCLK); also elsewhere on the board
NRFSWDIO: J12.1, U8.44 (SWDIO); also elsewhere on the board
NRFTX: U8.6 (P0.25); also elsewhere on the board
NRFUSBD+: J15.3 (D+), U8.68 (USB-D+)
NRFUSBD-: J15.2 (D-), U8.67 (USB-D-)
unnamed: D3.2 (A), R15.2
unnamed: D4.2 (A), R16.2
unnamed: R15.1, U8.38 (P0.20)
unnamed: R16.1, U8.36 (P0.21)
SCL: U8.10 (P0.29); also elsewhere on the board
SDA: U8.9 (P0.28); also elsewhere on the board
VCC: C14.1, U8.17 (VCC1), U8.65 (VCCH1); also elsewhere on the board

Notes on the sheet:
USB power

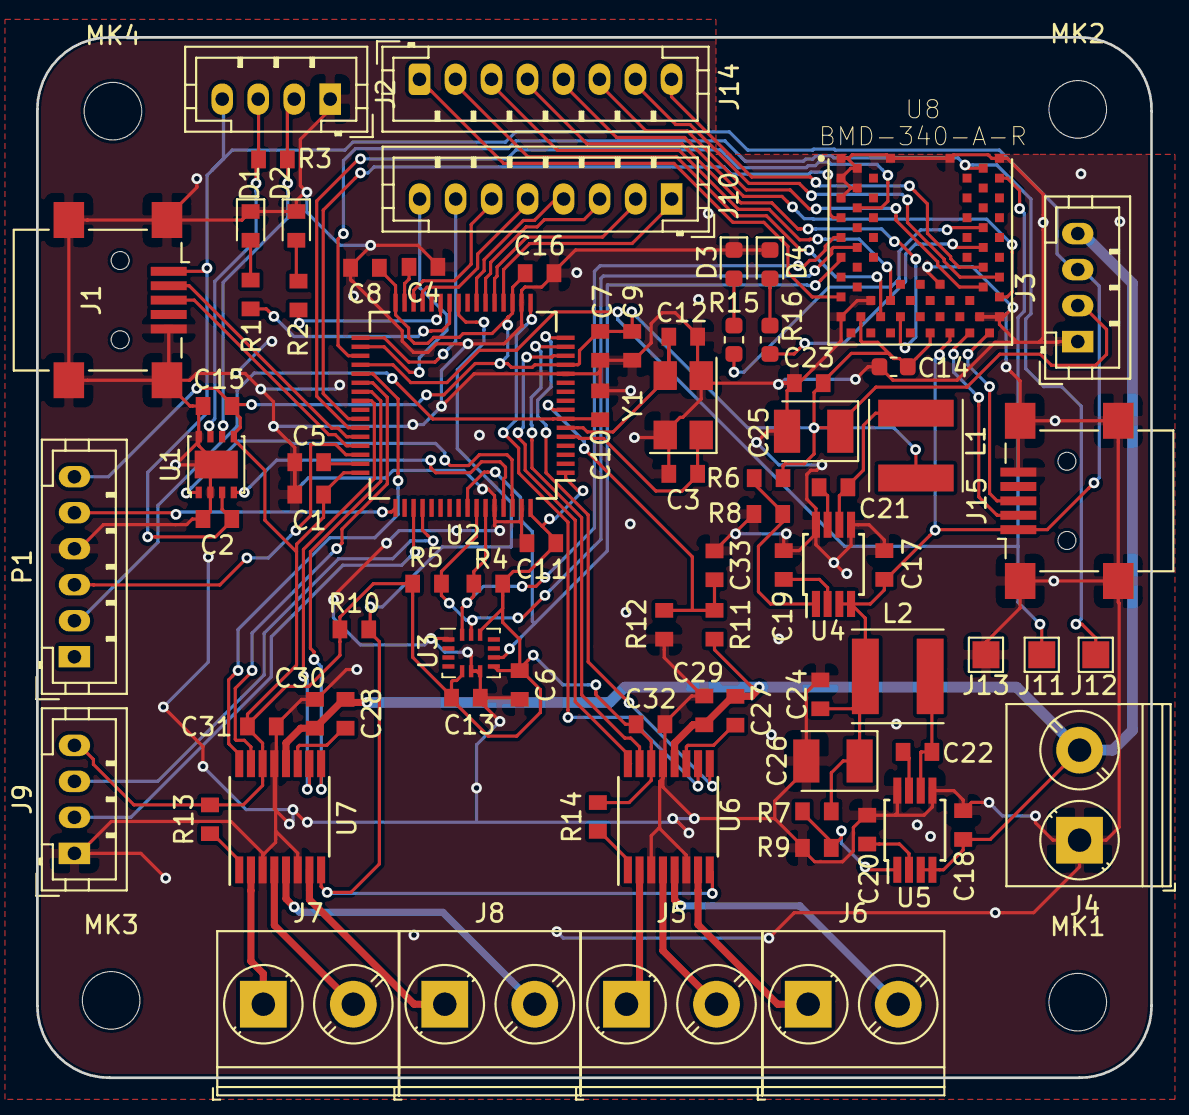
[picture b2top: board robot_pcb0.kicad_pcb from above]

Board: 2 copper layers, 61.9 x 57.8 mm, 84 parts (0 on the bottom side), 82 nets.

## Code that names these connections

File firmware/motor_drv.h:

/*
    Copyright 2019 Joel Svensson	svenssonjoel@yahoo.se

    This program is free software: you can redistribute it and/or modify
    it under the terms of the GNU General Public License as published by
    the Free Software Foundation, either version 3 of the License, or
    (at your option) any later version.

    This program is distributed in the hope that it will be useful,
    but WITHOUT ANY WARRANTY; without even the implied warranty of
    MERCHANTABILITY or FITNESS FOR A PARTICULAR PURPOSE.  See the
    GNU General Public License for more details.

    You should have received a copy of the GNU General Public License
    along with this program.  If not, see <http://www.gnu.org/licenses/>.
*/
#ifndef _MOTOR_DRV_H_
#define _MOTOR_DRV_H_

/* Information

   2x DRV8833 - four motors

   DRV8833-1:  (TIM2)
   AIN1 - PA0
   AIN2 - PA1
   BIN1 - PA2
   BIN2 - PA3

   DRV8833-2:  (TIM3)
   AIN1 - PC6
   AIN2 - PC7
   BIN1 - PC8
   BIN2 - PC9

   xIN1    |  xIN2   |   Function
   PWM     |   0     |   Forward PWM - fast decay
    1      |  PWM    |   Forward PWM - slow decay
    0      |  PWM    |   Backwards PWM - fast decay
   PWM     |   1     |   Backwards PWM - slow decay

 */

extern void drv_init(void);

#endif
